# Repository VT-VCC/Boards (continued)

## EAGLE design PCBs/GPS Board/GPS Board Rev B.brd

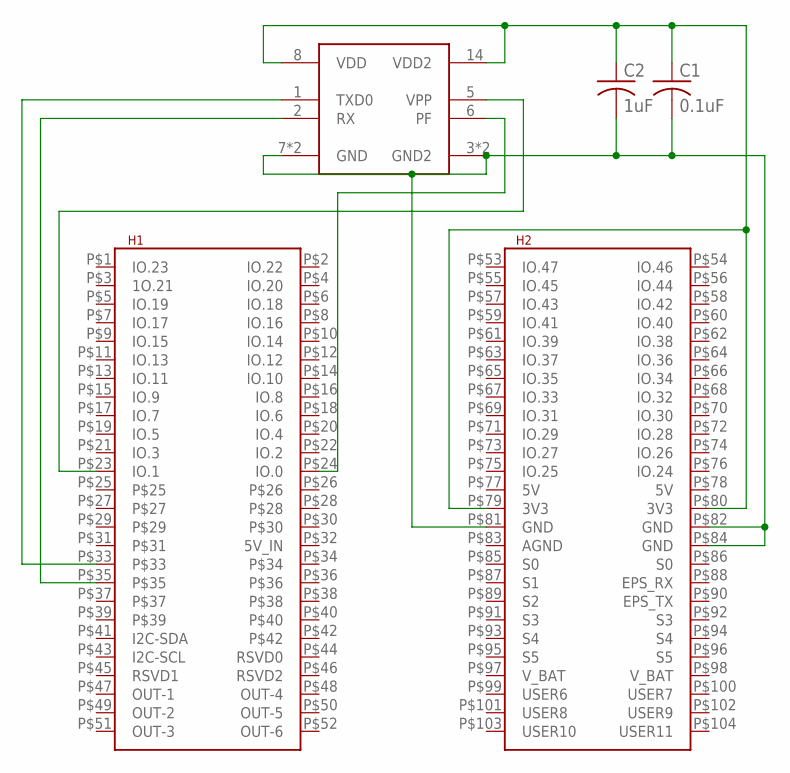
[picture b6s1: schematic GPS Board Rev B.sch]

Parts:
C1: 0.1uF; C0603
C2: 1uF; C0603
U$1: PINAVL1; PINAV-L1
U$2: PC104

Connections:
GND: C1.2, C2.2, U$1.3 (GND2), U$1.7 (GND), U$1.15 (GND2), U$1.16 (GND), U$2.P$81 (GND), U$2.P$82 (GND), U$2.P$84 (GND)
unnamed: U$1.5 (VPP), U$2.P$23 (IO.1)
unnamed: U$1.6 (PF), U$2.P$24 (IO.0)
unnamed: C1.1, C2.1, U$1.8 (VDD), U$1.14 (VDD2), U$2.P$79 (3V3), U$2.P$80 (3V3)
unnamed: U$1.1 (TXD0), U$2.P$33
unnamed: U$1.2 (RX), U$2.P$35

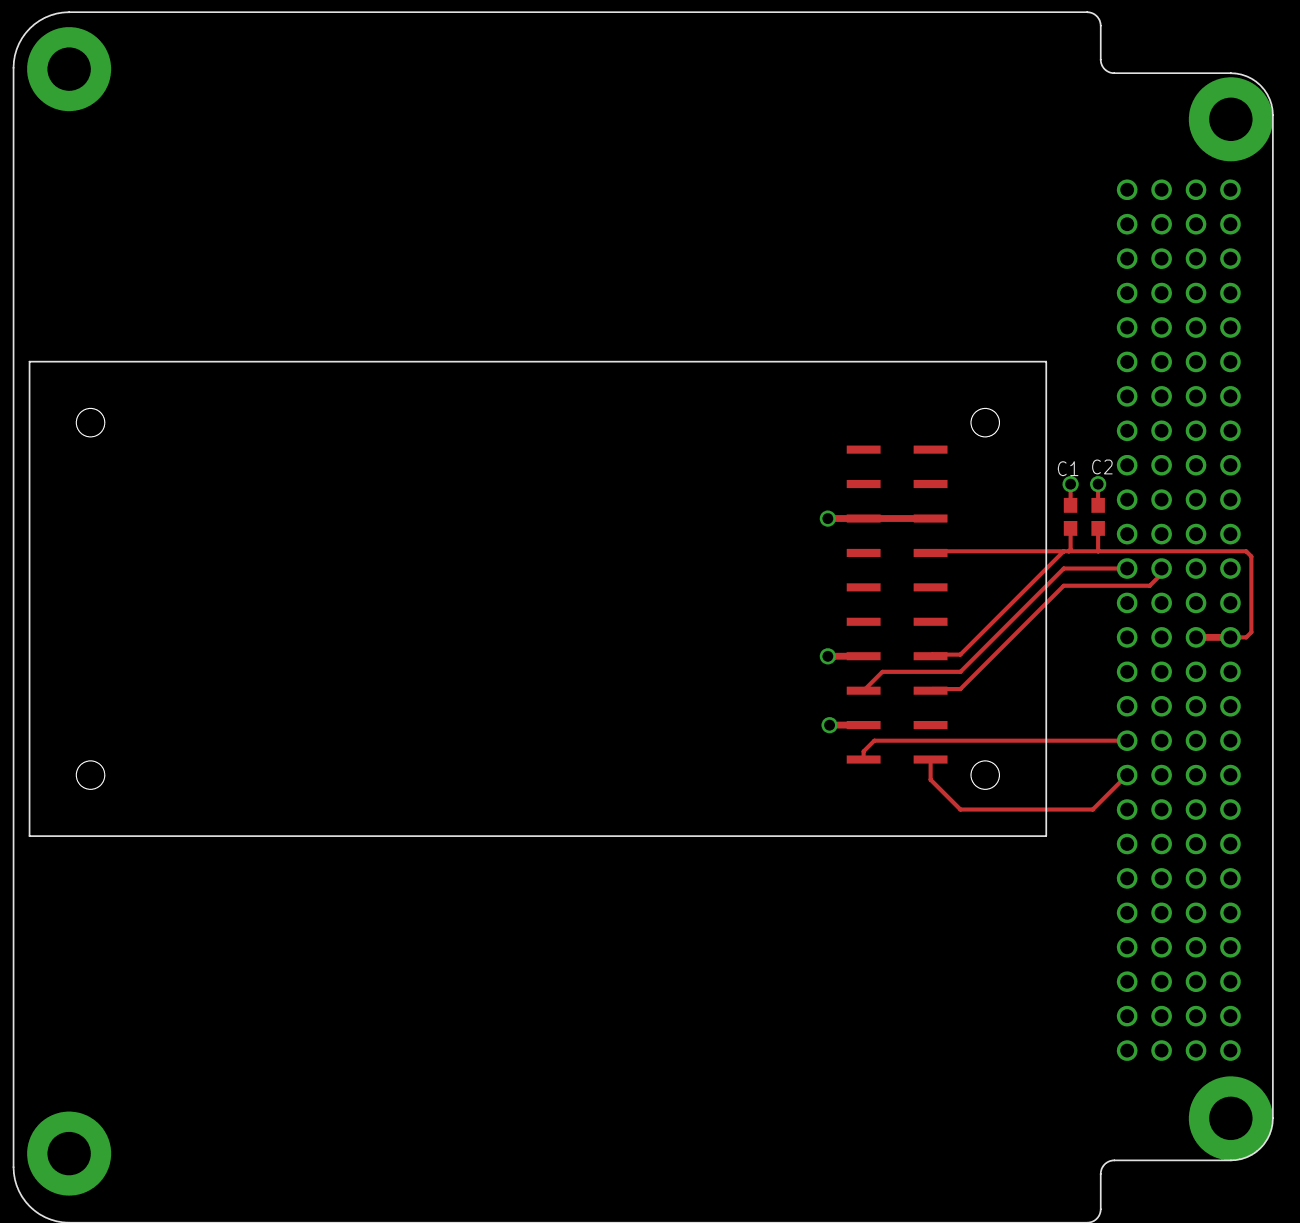
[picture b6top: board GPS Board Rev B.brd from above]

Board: 2 copper layers, 4 parts (0 on the bottom side), 6 nets.

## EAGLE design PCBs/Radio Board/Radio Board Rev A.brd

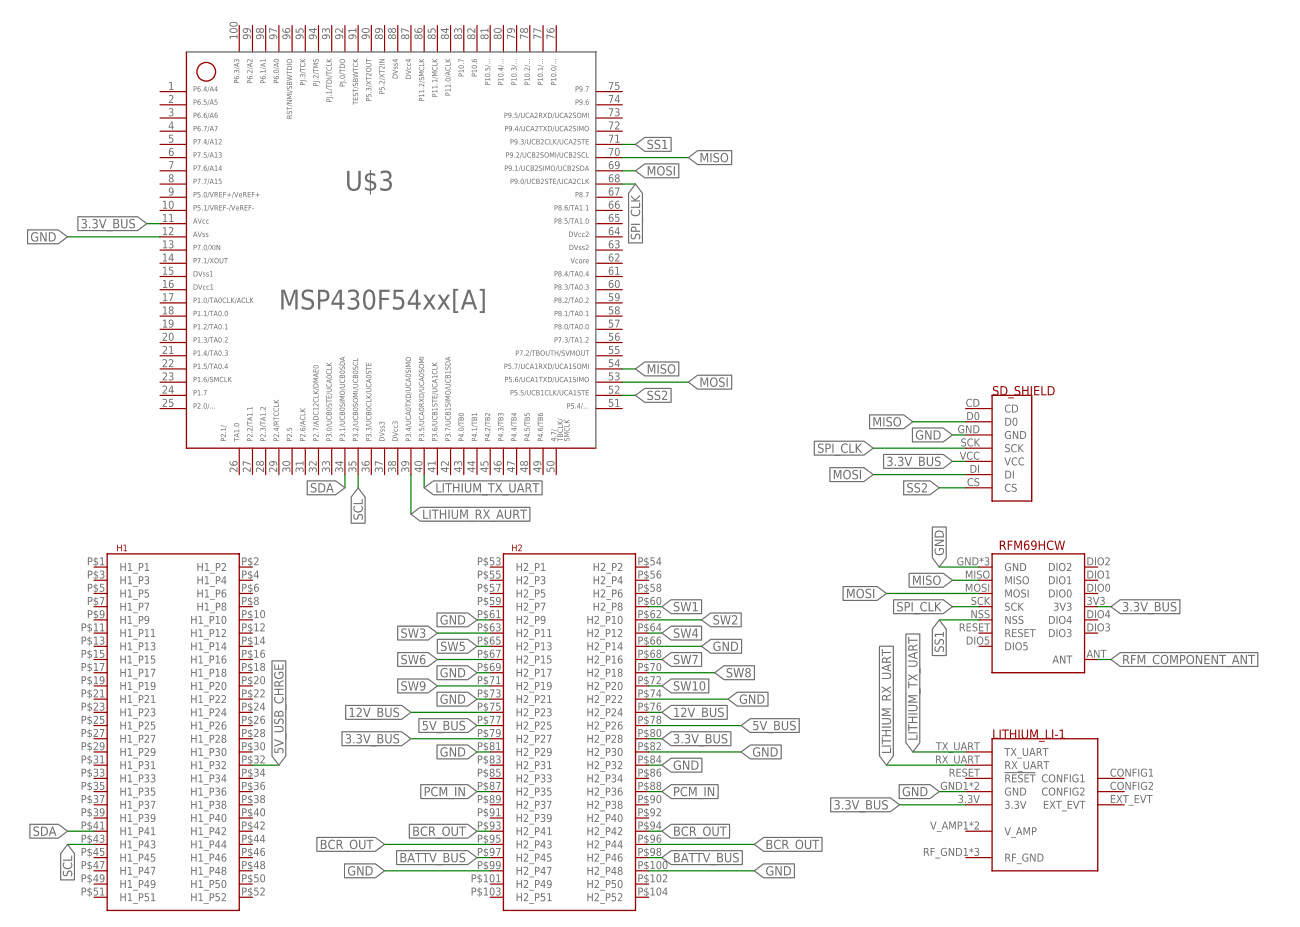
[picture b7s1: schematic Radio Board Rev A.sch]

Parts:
U$1: LITHIUM; LI-1
U$2: PC104
U$3: MSP430F5438A; PZ100
U$4: RFM69HCWSMT; RFM69HCW-SMT
U$5: SD_SHIELD

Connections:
3.3V_BUS: U$1.3.3V, U$2.P$79 (H2_P27), U$2.P$80 (H2_P28), U$3.11, U$4.3V3, U$5.VCC
5V_BUS: U$2.P$77 (H2_P25), U$2.P$78 (H2_P26)
5V_USB_CHRGE: U$2.P$32 (H1_P32)
12V_BUS: U$2.P$75 (H2_P23), U$2.P$76 (H2_P24)
15: U$3.15
16: U$3.16
37: U$3.37
38: U$3.38
62: U$3.62
63: U$3.63
64: U$3.64
87: U$3.87
88: U$3.88
BATTV_BUS: U$2.P$97 (H2_P45), U$2.P$98 (H2_P46)
BCR_OUT: U$2.P$93 (H2_P41), U$2.P$94 (H2_P42), U$2.P$95 (H2_P43), U$2.P$96 (H2_P44)
GND: U$1.GND1 (GND), U$1.GND2 (GND), U$2.P$61 (H2_P9), U$2.P$66 (H2_P14), U$2.P$69 (H2_P17), U$2.P$73 (H2_P21), U$2.P$74 (H2_P22), U$2.P$81 (H2_P29), U$2.P$82 (H2_P30), U$2.P$84 (H2_P32), U$2.P$99 (H2_P47), U$2.P$100 (H2_P48), U$3.12, U$4.GND, U$4.GND@1 (GND), U$4.GND@2 (GND), U$5.GND
LITHIUM_RX_AURT: U$3.39
LITHIUM_RX_UART: U$1.RX_UART
LITHIUM_TX_UART: U$1.TX_UART, U$3.40
MISO: U$3.54, U$3.70, U$4.MISO, U$5.D0
MOSI: U$3.53, U$3.69, U$4.MOSI, U$5.DI
PCM_IN: U$2.P$87 (H2_P35), U$2.P$88 (H2_P36)
RFM_COMPONENT_ANT: U$4.ANT
SCL: U$2.P$43 (H1_P43), U$3.35
SDA: U$2.P$41 (H1_P41), U$3.34
SPI_CLK: U$3.68, U$4.SCK, U$5.SCK
SS1: U$3.71, U$4.NSS
SS2: U$3.52, U$5.CS
SW1: U$2.P$60 (H2_P8)
SW2: U$2.P$62 (H2_P10)
SW3: U$2.P$63 (H2_P11)
SW4: U$2.P$64 (H2_P12)
SW5: U$2.P$65 (H2_P13)
SW6: U$2.P$67 (H2_P15)
SW7: U$2.P$68 (H2_P16)
SW8: U$2.P$70 (H2_P18)
SW9: U$2.P$71 (H2_P19)
SW10: U$2.P$72 (H2_P20)

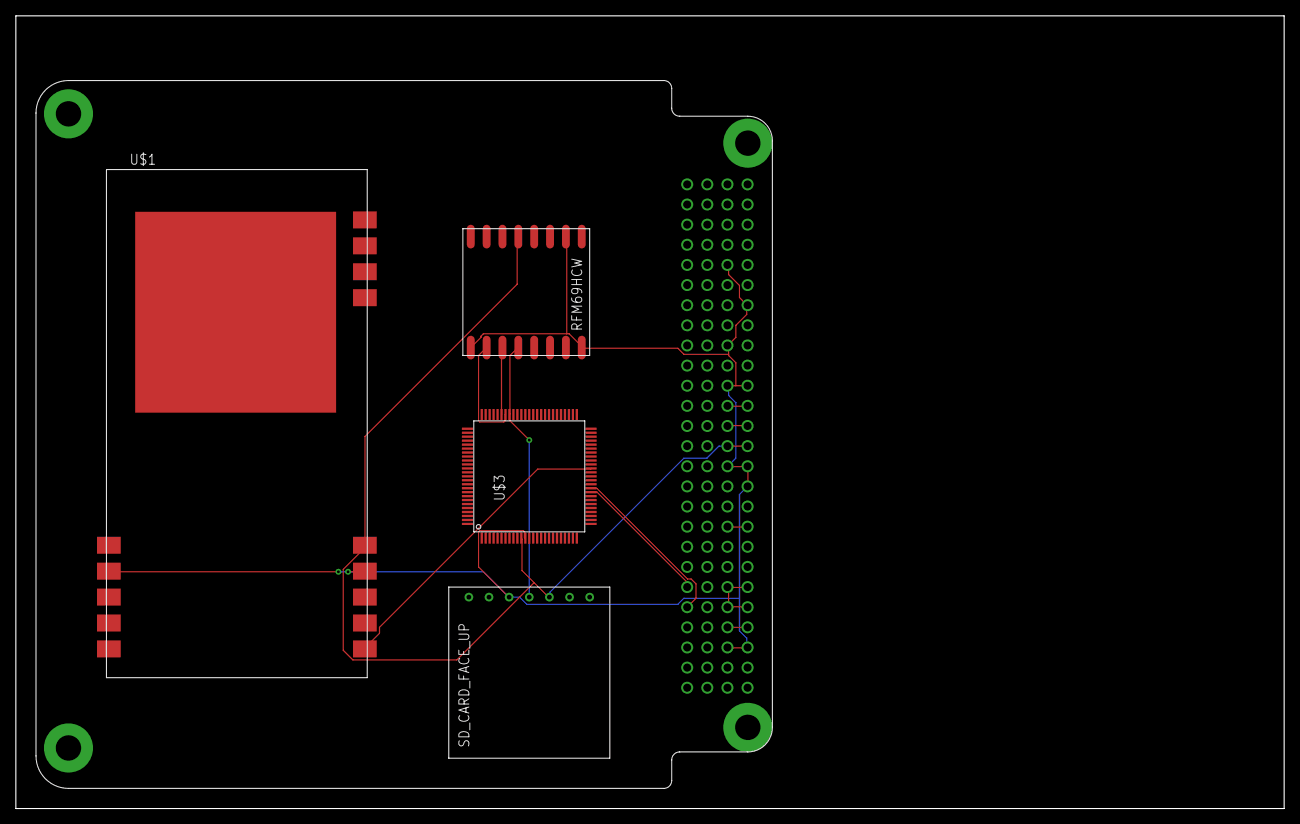
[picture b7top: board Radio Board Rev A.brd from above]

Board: 2 copper layers, 160.0 x 100.0 mm, 5 parts (0 on the bottom side), 15 nets.

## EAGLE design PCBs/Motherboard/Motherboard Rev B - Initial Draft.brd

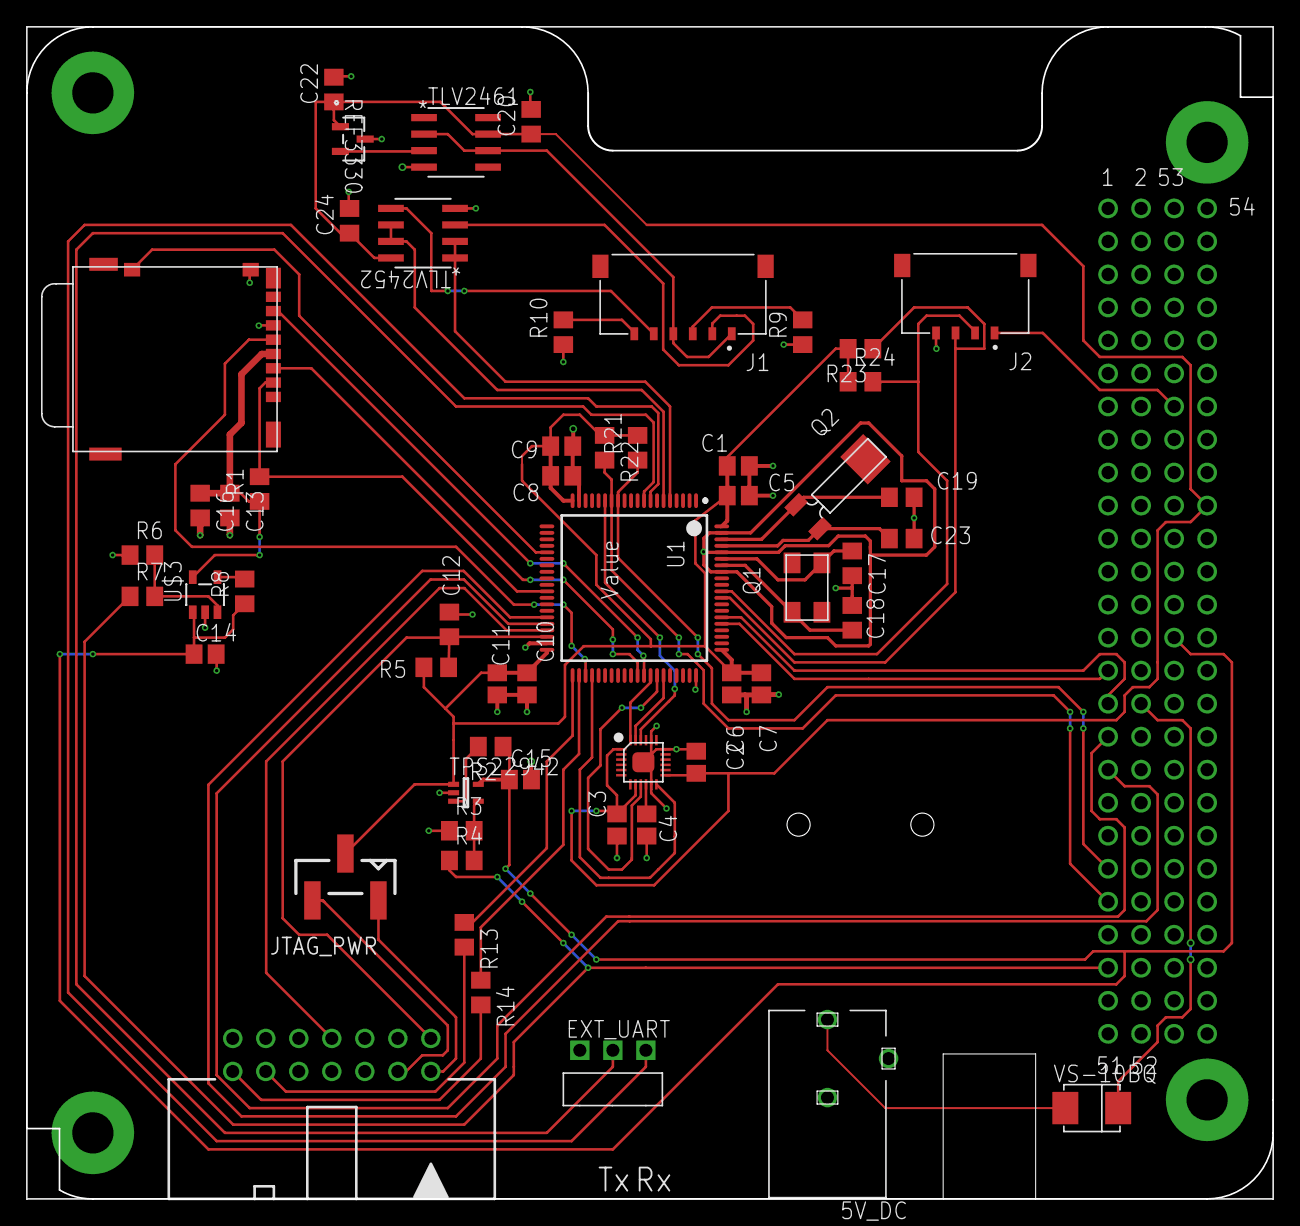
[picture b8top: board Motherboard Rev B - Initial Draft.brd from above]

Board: 2 copper layers, 95.9 x 90.2 mm, 58 parts (0 on the bottom side), 56 nets.

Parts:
5V_DC: PJ-102A; CUI_PJ-102A
C1, C2, C4, C6, C8, C10, C16, C20, C22, C24: 0.1uF; C0805
C3: 10nF; C0805
C5, C7, C9, C11: 1uF; C0805
C12: 1nF; C0805
C13, C14, C15: 10uF; C0805
C17, C18: 35pF; C0805
C19, C23: 12pF; C0805
EXT_UART: 90121-0763
J1: MOLEX_504050-0691; MOLEX_5040500691
J2: MOLEX_504050-0491; MOLEX_5040500491
JTAG_PWR: MOLEX_SL_03-87898; SL_87898_3
Q1: 16M; 5X3.2
Q2: 32.768k; MS1V-T1K
R1, R5: 47k; R0805
R2, R3, R6, R8: 100k; R0805
R4, R7, R13, R14: 0; R0805
R9, R10: 100; R0805
R21, R22, R23, R24: 10k; R0805
RBF_MOUNT: RBF_MOUNT
REF3330: REF3330_DBZ_3; DBZ3
SD_CONN: 502702-0891; 502702
TLV2452: TLV2452; D8
TLV2461: TLV2461A_D_8; D8
TPS22942: TPS22942DCKR; DCK0005A
U1: Value; PN0080A_N
U$1: PC104_NO_DIMENSION
U$2: MPU-9250; LEAD-QFN24
U$3: FPF2105; SOT23-5
VS-10BQ: 10BQ015HM3; SMB
X1: 2514-5; PAK100/2500-5-14

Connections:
3V: J1.1, J1.4, TLV2461.2, TLV2461.6
3V3: C14.1, C15.1, R2.1, R8.1, TPS22942.5, U$1.79, U$3.1
3V3_SD: C13.1, C16.1, R1.1, SD_CONN.4, U$3.5
3V3_UC: C1.1, C5.1, C6.1, C7.1, C8.1, C9.1, C10.1, C11.1, JTAG_PWR.2, R5.2, R21.2, R22.1, R23.2, R24.1, TPS22942.1, U1.20, U1.40, U1.61, U1.80
3V_REF: REF3330.2, TLV2461.3
5V_CHG: U$1.32, VS-10BQ.C
AGND: C1.2, C5.2, C17.2, C18.2, C19.2, C23.2, U1.73, U1.76, U1.79, U$1.61, U$1.66, U$1.69, U$1.74
CLK_IMU: U1.55, U$2.23
CLK_SD: SD_CONN.5, U1.43
CS_IMU: U1.15, U$2.22
CS_SD: R1.2, SD_CONN.2, U1.31
EXT_RXD: EXT_UART.3, U1.8
EXT_TXD: EXT_UART.2, U1.9
GND: 5V_DC.2, 5V_DC.3, C2.2, C3.2, C4.2, C6.2, C7.2, C8.2, C9.2, C10.2, C11.2, C12.2, C13.2, C14.2, C15.2, C16.2, C20.2, C22.2, C24.2, EXT_UART.1, J2.4, R3.1, R6.1, R9.1, R10.1, REF3330.3, SD_CONN.6, SD_CONN.GND, TLV2452.4, TLV2461.4, TPS22942.2, U1.19, U1.39, U1.60, U$1.73, U$1.81, U$1.82, U$1.84, U$1.99, U$1.100, U$2.11, U$2.18, U$2.20, U$2.25, U$3.2, X1.9
INT_IMU: U1.44, U$2.12
JTAG_RXD: R13.1, U1.41
JTAG_TXD: R14.1, U1.42
LITHIUM_RX: U1.65, U$1.29
LITHIUM_TX: U1.66, U$1.31
LI_OA_RESET: R4.1, R7.1, U$1.47
MISO_IMU: U1.54, U$2.9
MISO_SD: SD_CONN.7, U1.52
MOSI_IMU: U1.53, U$2.24
MOSI_SD: SD_CONN.3, U1.51
unnamed: R2.2, TPS22942.3
unnamed: R6.2, R7.2, U$3.3
unnamed: C4.1, U$2.10
unnamed: C17.1, Q1.1, U1.75
unnamed: R3.2, R4.2, TPS22942.4
unnamed: R8.2, U$3.4
unnamed: R14.2, X1.14
unnamed: C23.1, Q2.1, U1.77
unnamed: R13.2, X1.12
unnamed: C18.1, Q1.2, U1.74
unnamed: C19.1, Q2.2, U1.78
unnamed: 5V_DC.1, VS-10BQ.A
PINAVL1_RX: U1.35, U$1.35
PINAVL1_TX: U1.36, U$1.33
SBWTCK: U1.37, X1.7
SBWTDIO: C12.1, R5.1, U1.38, X1.1
SCL_ANT: J2.2, R24.2, U1.70
SCL_EPS: R22.2, U1.14, U$1.43
SDA_ANT: J2.3, R23.1, U1.69
SDA_EPS: R21.1, U1.13, U$1.41
SD_DETECT: SD_CONN.DET, U1.25
SHIELD: J1.SH1, J1.SH2, J2.SH1, J2.SH2
SW5: J2.1, U$1.65
SW10: C2.1, C3.1, C20.1, C22.1, C24.1, REF3330.1, TLV2452.8, TLV2461.7, U$1.72, U$2.1, U$2.8, U$2.13
TMP1: J1.2, TLV2452.3
TMP1_OUT: TLV2452.1, TLV2452.2, U1.5
TMP1_RET: J1.3, R9.2
TMP2: J1.5, TLV2452.5
TMP2_OUT: TLV2452.6, TLV2452.7, U1.6
TMP2_RET: J1.6, R10.2
VCC_TARGET: JTAG_PWR.3, X1.4
VCC_TOOL: JTAG_PWR.1, X1.2

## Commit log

2018-06-28 Add PCBs and working revs
2018-07-03 Added bypass caps to radio
2018-07-03 Changed GPS power source to an EPS PDM, tweaked trace width
2018-07-03 Updated pin-mappings, added SD card
2018-07-03 Changed SD card connector
2018-07-03 Add interfacing references
2018-07-03 Ignore library backup and spreadsheet lock files
2018-07-03 Add SOIC 8 AD590KRZ part
2018-07-03 Update AD590 package silkscreen
2018-07-03 Fix schematic origin
2018-07-03 Add temp sensors to GPS and Radio boards
2018-07-04 Temp sensor pins
2018-07-04 Created load-switching MOSFET (for SD card)
2018-07-04 Updated mobo, began mobo layout
2018-07-05 Corrected IMU pinout
2018-07-05 Add SD Card
2018-07-05 Fixed temp sens pin error
2018-07-05 First working draft... still missing sensing and JTAG elements
2018-07-05 Rotated GPS, bumped cap to 10uF
2018-07-06 Changed Li Tx/Rx pins
2018-07-06 Added OSH Park design rules
2018-07-06 Remove temp sensors, move radio and uC to 3V3 bus
2018-07-07 Remove temp sensor, tweak trace width
2018-07-07 Remove temp sensors, tweak trace width
2018-07-07 Replace components with 0805s
2018-07-07 Make GPS board pass ERC and DRC
2018-07-09 Added Lithium OA system reset
2018-07-10 Add combined Radio/GPS board, if needed
2018-07-10 Add centralized library with Li, PC104, piNAV
2018-07-10 Update radio board to use new library
2018-07-10 Add old versions of parts to library
2018-07-10 Add MicroSD, Hirose, and TPS22942 parts
2018-07-11 Use different PC104 footprints for each board
2018-07-11 Update GPS board to use new library
2018-07-11 Missed a connection
2018-07-11 Fix thermal/ground connection of radio
2018-07-11 Replace motherboard footprint with new library
2018-07-11 Update cap values
2018-07-11 Add Samtec footprints
2018-07-12 Use common PC104 footprint with dimensions set per board
2018-07-12 Add hardware interfaces for radio, GPS
2018-07-13 Add test pads
2018-07-13 Add TI REF3330 voltage reference part
2018-07-13 Added DF11-4DP connector part
2018-07-13 Add Molex connector and connector bypass to radio board
2018-07-13 Correct Molex connection
2018-07-14 Move MicroLock connector
2018-07-14 Rearrange pins to keep traces only on topside
2018-07-17 So. many. changes.
2018-07-18 Update piNAV connector to PE-BE model
2018-07-19 Add some opamps
2018-07-19 Update bus definition, connectors
2018-07-19 Split I2C and SPI buses
2018-07-19 Add SD card detect to 7.2
2018-07-19 Fix trace collision
2018-07-19 Update bus definition
2018-07-20 Replace SD connector with a model hand-solderable
2018-07-20 Add SD card drawing
2018-07-20 Add HFXtal
2018-07-20 Use 5-pin Pico-Lock for sensor harness
2018-07-20 Changed opamps used in sensing circuits
2018-07-21 Ignore gerber zips
2018-07-21 Improve decoupling, ground impedance, silkscreens
2018-07-21 Remove trace stubs
2018-07-21 Add OSH Park CAM config
2018-07-21 Minor silkscreen changes
2018-07-21 Add testpads, improve bypassing, update routing
2018-07-22 Add xtals, antenna harness, finish most wiring
2018-07-23 Add I2C pullups
2018-07-23 Move SD, make room for RBF
2018-07-24 Add external 5V charging jack
2018-07-25 Add Li-2 device
2018-07-25 Replace radio with Li-2 footprint
2018-07-25 Swap JTAG UART and piNAV comm channels
2018-07-25 Align origin to center of footprint
2018-07-25 Add Molex 3-pin breakaway footprint
2018-07-25 Add external UART connector
2018-07-26 Shrink pads to not short RBF mount
2018-07-26 Add RBF mount footprint
2018-07-26 Update keepout zone
2018-07-26 Add 6 position Pico-Lock
2018-07-26 Add RBF mount, replace strain gauge with temp sensor, clean up crossed traces, dimension PCB to accomodate wiring
2018-07-26 Update sidewall temp pin assignments
2018-07-26 Add Antenna and update IMU
2018-07-26 Remove antenna I2C pins from bus
2018-07-27 First draft
2018-07-27 Rework layout for tighter traces
2018-07-27 Add hatching to demark RBF pin housing
2018-07-27 Completed first draft
2018-07-28 Remove initial draft
2018-07-28 Remove outline cuts for inhibits
2018-08-01 Add Hirose DF13
2018-08-01 Update header pin labels
2018-08-01 Add rev info to silkscreen
2018-08-01 Add test pads, RBF->DF13 wiring, update power distribution, breakout extra I/O pins
2018-08-01 Update silkscreen with VT logo
2018-08-01 Add NC pin from RBF
2018-08-02 Add Lithium reset pin
2018-08-02 Add pin numbers to bottom silkscreen
2018-08-02 Rev A Final
2018-08-02 Add Lithium Reset, GPS PF and VPP
2018-08-02 Rev B final take 1
2018-08-02 Rev A2
2018-08-02 Thermally couple radio to chassis
2018-08-02 Add mount pads to PC104 symbol
2018-08-02 Pass DRC
2018-08-03 Correct milling and pads for elongated pins
2018-08-03 Replace hatching with outline for RBF pin
2018-08-03 Use only 8mil traces
2018-08-04 Create comm parts list
2018-10-17 Update drill sizes
2018-10-17 Mobo Rev C Initial Commit
2019-01-28 Updated the readme
